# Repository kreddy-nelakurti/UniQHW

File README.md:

# UniQHW

The hardware repository for UQ Phone (UniQ)
The Corresponding software component can be found [https://github.com/Benksur/UniQOS](https://github.com/Benksur/UniQOS)

## About

**Supervised by:** Professor Pauline Pounds  
**Institution:** University of Queensland
<div align="center">

### UQ Phone Team (Year 1 - 2025)

| Name | Role |
|------|------|
| **Ty Behnke** | Firmware Design |
| **James Wood** | Hardware Design |
| **Caiyan Jin** | UI/UX Design |
</div>

Any Questions about the PCB and Schematics please direct them to [james.brian.wood@outlook.com](james.brian.wood@outlook.com)

## Production

The V0.2.0 PCB's must be made with the following specifications from JLCPCB

### Main PCB

This 6-Layer PCB must be made with the following

- Via Covering:	Epoxy Filled & Capped
- Min via hole size/diameter:	0.2mm/(0.3/0.35mm)

The following are also required if meeting the full size specifications of UniQ

- PCB Thickness:	0.8mm

Production versions should also be made with the following (Dependant on desired finish)

- Surface Finish:	ENIG Gold Thickness: 2U"
- PCB Color:	Black
- Silkscreen:	White

### Secondary PCB (Cellular Board)

This 4-Layer PCB must be made with the following

- PCB Thickness:	0.6mm
- Via Covering:	Epoxy Filled & Capped
- Min via hole size/diameter:	0.2mm/(0.3/0.35mm)
- Specify Stackup:	yes JLC04061H-2116

If Either the thickness or stackup is to change this boards traces should be redesigned for 50Ohm Impedance 

Production versions should also be made with the following (Dependant on desired finish)

- Surface Finish:	ENIG Gold Thickness: 2U"
- PCB Color:	Black
- Silkscreen:	White

## Current Issues And Improvements

The V0.2.0 PCB currently suffers from several issues which should be rectified on later versions:

- Batter Connector Location: move so it can be inserted and removed indpendantly of the secondary PCB
- SD/SIM Socket: Tie 3.3v SD card rail to insertion detection to prevent hot-plugging
- Debug Pads: Consider moving to provide easier access without interferance from screen
- Soft Power: Add soft power switch for more agressive power-off functionality and safer power-downs

The following may also be investigated for benefit 
- Improve Display: Ideally Display utilises a parellel interface, this needs more investigation
- Audio Volume: Current speaker is quiet, this should be investigated further to see if this can be remediated in firmware first
- USB Support: Add USB data connectivity to the device for file transfer or programming, this may resolve debug pad issues
- BT Audio: this poses significant challenges, although may be worth while, investigate further

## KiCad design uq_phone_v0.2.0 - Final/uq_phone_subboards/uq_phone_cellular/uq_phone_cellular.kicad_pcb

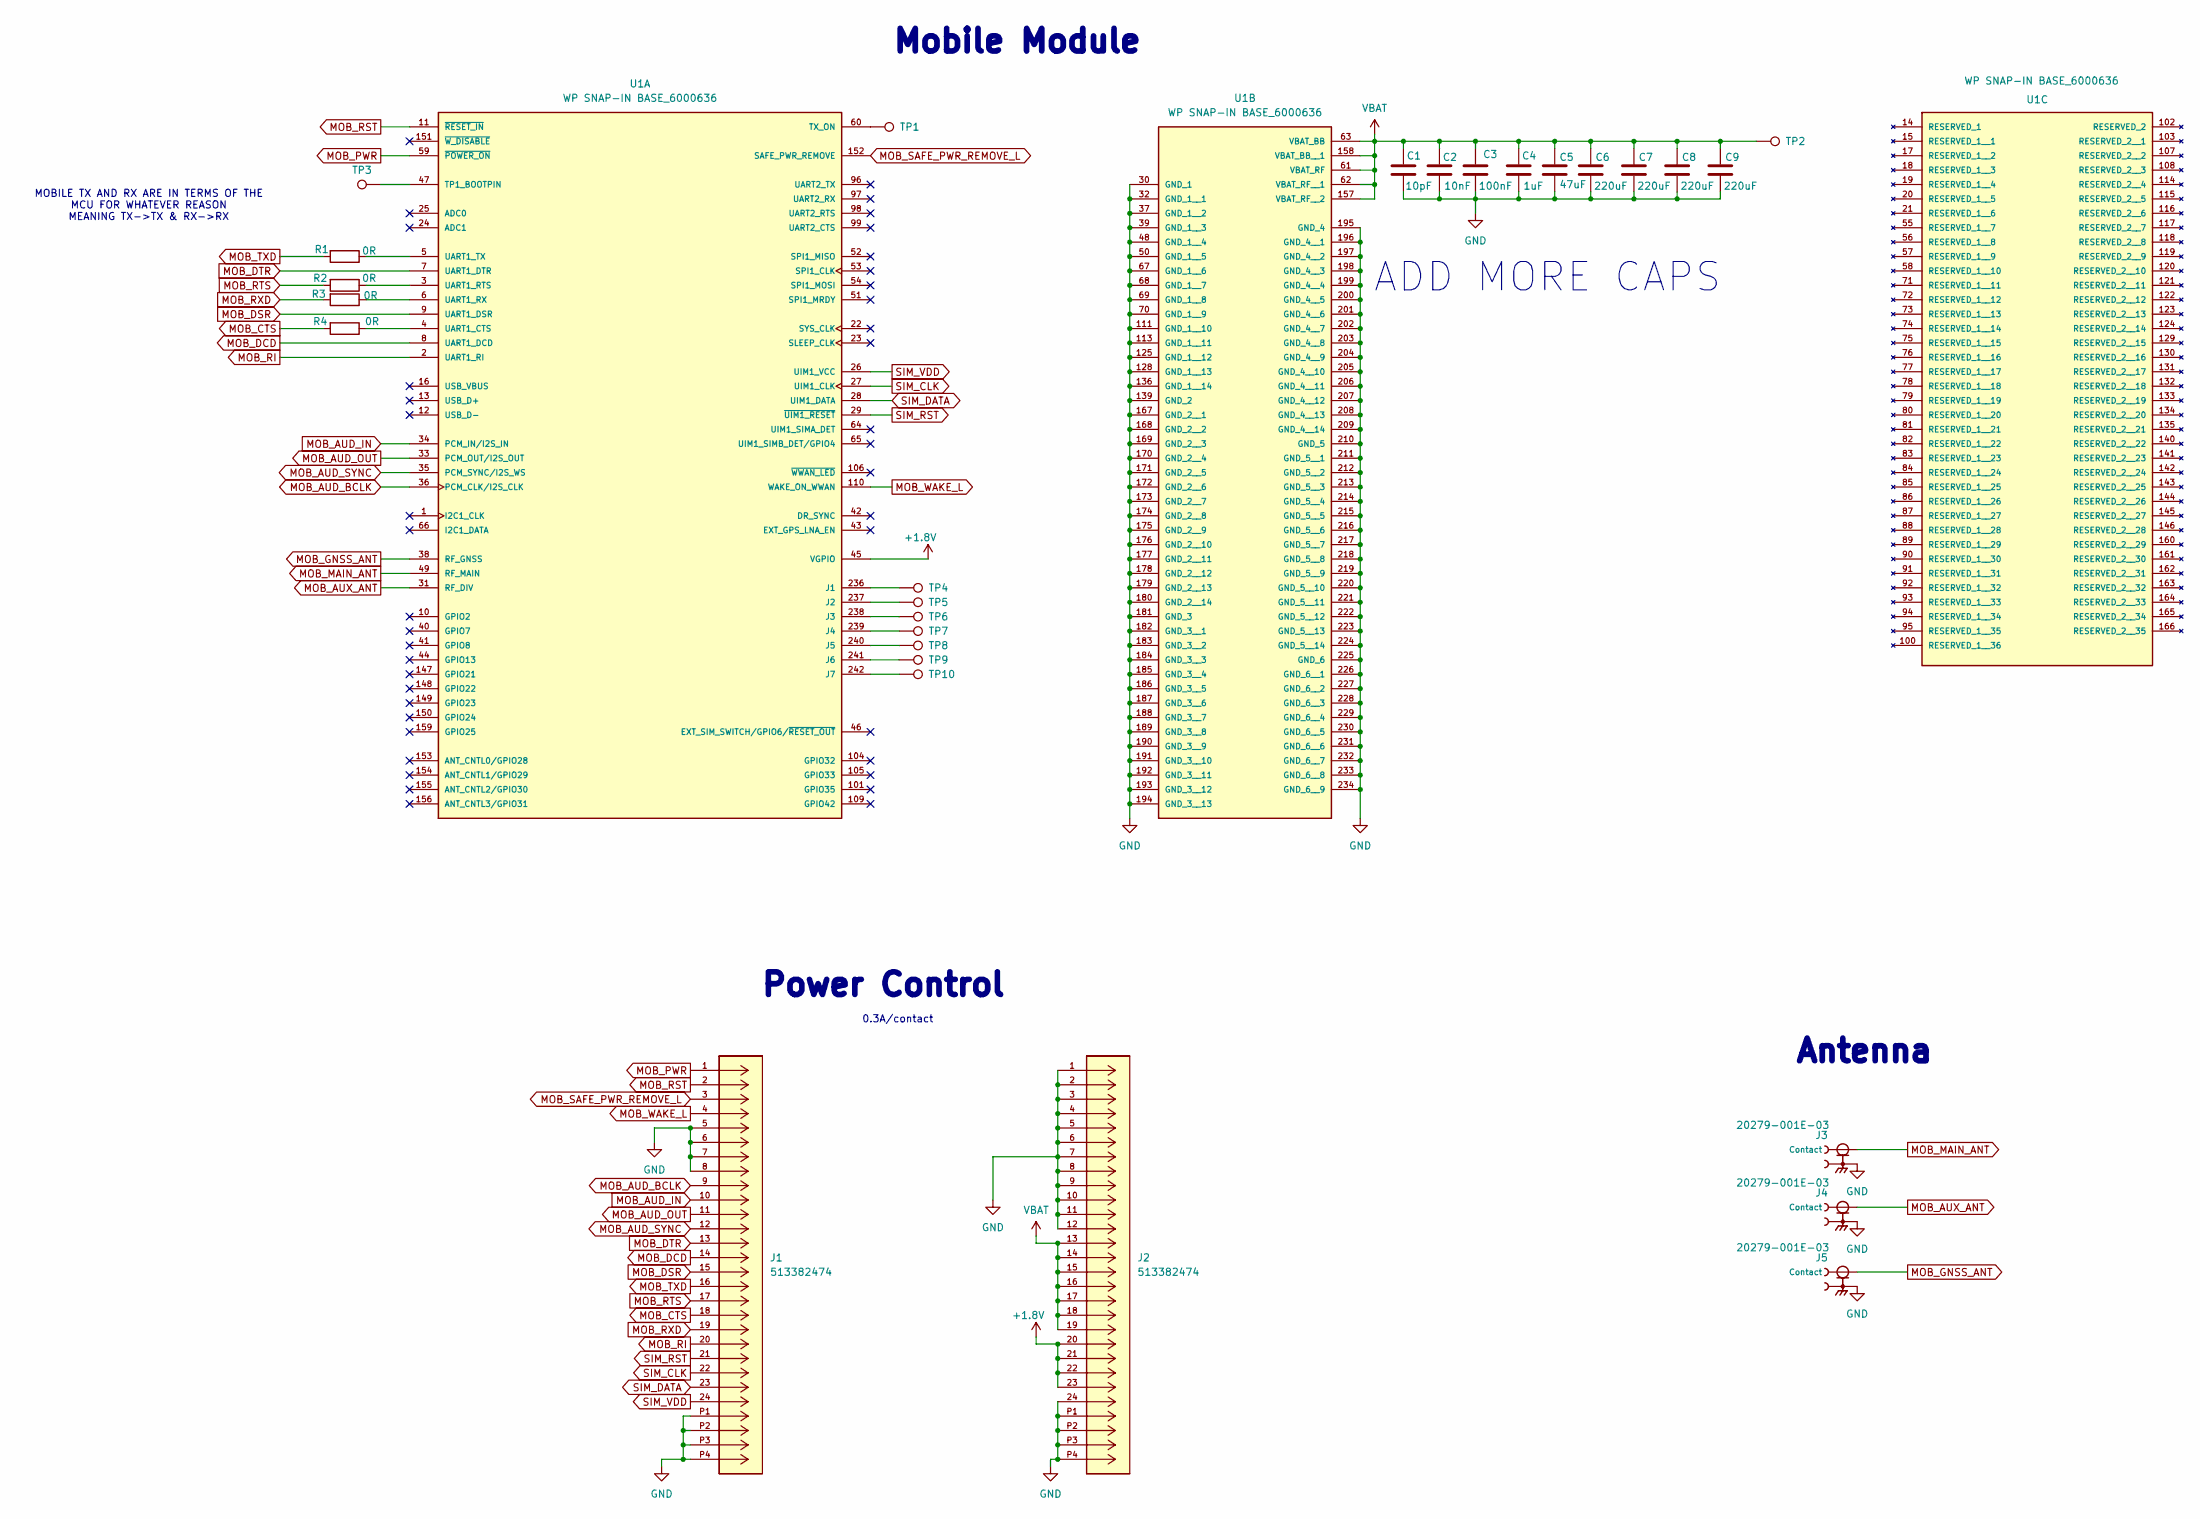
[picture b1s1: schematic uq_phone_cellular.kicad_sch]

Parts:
C1: 10pF; C_0402_1005Metric; LCSC PN C2168222
C2: 10nF; C_0402_1005Metric; LCSC PN C15195
C3: 100nF; C_0201_0603Metric; LCSC PN C160831
C4: 1uF; C_0201_0603Metric; LCSC PN C53067
C5: 47uF; C_0805_2012Metric; LCSC PN C109461
C6, C7, C8, C9: 220uF; C_1206_3216Metric; LCSC PN C412252
J1, J2: 513382474; CON_513382474; MANUFACTURER_PART_NUMBER 513382474; DigiKey_Part_Number WM8960TR-ND
J3, J4, J5: 20279-001E-03; IPEX_20279-001E-03; PARTREV 32; LCSC PN C36499136
R1, R2, R3, R4: 0R; R_0402_1005Metric; LCSC PN C60485
TP1, TP2, TP3, TP4, TP5, TP6, TP7, TP8, TP9, TP10: TestPoint; TestPoint_Pad_D1.5mm
U1: WP SNAP-IN BASE_6000636; XCVR_RC7620_1104625; PARTREV 12

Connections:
+1.8V: J2.20, J2.21, J2.22, J2.23, U1.45 (VGPIO)
GND: C1.2, C2.2, C3.2, C4.2, C5.2, C6.2, C7.2, C8.2, C9.2, J1.5, J1.6, J1.7, J1.8, J1.P1, J1.P2, J1.P3, J1.P4, J2.1, J2.2, J2.3, J2.4, J2.5, J2.6, J2.7, J2.8, J2.9, J2.10, J2.11, J2.12, J2.24, J2.P1, J2.P2, J2.P3, J2.P4, J3.2, J4.2, J5.2, U1.30 (GND_1), U1.32 (GND_1__1), U1.37 (GND_1__2), U1.39 (GND_1__3), U1.48 (GND_1__4), U1.50 (GND_1__5), U1.67 (GND_1__6), U1.68 (GND_1__7), U1.69 (GND_1__8), U1.70 (GND_1__9), U1.111 (GND_1__10), U1.113 (GND_1__11), U1.125 (GND_1__12), U1.128 (GND_1__13), U1.136 (GND_1__14), U1.139 (GND_2), U1.167 (GND_2__1), U1.168 (GND_2__2), U1.169 (GND_2__3), U1.170 (GND_2__4), U1.171 (GND_2__5), U1.172 (GND_2__6), U1.173 (GND_2__7), U1.174 (GND_2__8), U1.175 (GND_2__9), U1.176 (GND_2__10), U1.177 (GND_2__11), U1.178 (GND_2__12), U1.179 (GND_2__13), U1.180 (GND_2__14), U1.181 (GND_3), U1.182 (GND_3__1), U1.183 (GND_3__2), U1.184 (GND_3__3), U1.185 (GND_3__4), U1.186 (GND_3__5), U1.187 (GND_3__6), U1.188 (GND_3__7), U1.189 (GND_3__8), U1.190 (GND_3__9), U1.191 (GND_3__10), U1.192 (GND_3__11), U1.193 (GND_3__12), U1.194 (GND_3__13), U1.195 (GND_4), U1.196 (GND_4__1), U1.197 (GND_4__2), U1.198 (GND_4__3), U1.199 (GND_4__4), U1.200 (GND_4__5), U1.201 (GND_4__6), U1.202 (GND_4__7), U1.203 (GND_4__8), U1.204 (GND_4__9), U1.205 (GND_4__10), U1.206 (GND_4__11), U1.207 (GND_4__12), U1.208 (GND_4__13), U1.209 (GND_4__14), U1.210 (GND_5), U1.211 (GND_5__1), U1.212 (GND_5__2), U1.213 (GND_5__3), U1.214 (GND_5__4), U1.215 (GND_5__5), U1.216 (GND_5__6), U1.217 (GND_5__7), U1.218 (GND_5__8), U1.219 (GND_5__9), U1.220 (GND_5__10), U1.221 (GND_5__11), U1.222 (GND_5__12), U1.223 (GND_5__13), U1.224 (GND_5__14), U1.225 (GND_6), U1.226 (GND_6__1), U1.227 (GND_6__2), U1.228 (GND_6__3), U1.229 (GND_6__4), U1.230 (GND_6__5), U1.231 (GND_6__6), U1.232 (GND_6__7), U1.233 (GND_6__8), U1.234 (GND_6__9)
MOB_AUD_BCLK: J1.9, U1.36 (PCM_CLK/I2S_CLK)
MOB_AUD_IN: J1.10, U1.34 (PCM_IN/I2S_IN)
MOB_AUD_OUT: J1.11, U1.33 (PCM_OUT/I2S_OUT)
MOB_AUD_SYNC: J1.12, U1.35 (PCM_SYNC/I2S_WS)
MOB_AUX_ANT: J4.1 (Contact), U1.31 (RF_DIV)
MOB_CTS: J1.18, R4.2
MOB_DCD: J1.14, U1.8 (UART1_DCD)
MOB_DSR: J1.15, U1.9 (UART1_DSR)
MOB_DTR: J1.13, U1.7 (UART1_DTR)
MOB_GNSS_ANT: J5.1 (Contact), U1.38 (RF_GNSS)
MOB_MAIN_ANT: J3.1 (Contact), U1.49 (RF_MAIN)
MOB_PWR: J1.1, U1.59 (~POWER_ON)
MOB_RI: J1.20, U1.2 (UART1_RI)
MOB_RST: J1.2, U1.11 (~RESET_IN)
MOB_RTS: J1.17, R2.2
MOB_RXD: J1.19, R3.2
MOB_SAFE_PWR_REMOVE_L: J1.3, U1.152 (SAFE_PWR_REMOVE)
MOB_TXD: J1.16, R1.2
MOB_WAKE_L: J1.4, U1.110 (WAKE_ON_WWAN)
unnamed: TP4.1, U1.236 (J1)
unnamed: TP5.1, U1.237 (J2)
unnamed: TP6.1, U1.238 (J3)
unnamed: TP7.1, U1.239 (J4)
unnamed: TP8.1, U1.240 (J5)
unnamed: TP9.1, U1.241 (J6)
unnamed: TP10.1, U1.242 (J7)
unnamed: TP3.1, U1.47 (TP1_BOOTPIN)
unnamed: TP1.1, U1.60 (TX_ON)
unnamed: R4.1, U1.4 (UART1_CTS)
unnamed: R2.1, U1.3 (UART1_RTS)
unnamed: R3.1, U1.6 (UART1_RX)
unnamed: R1.1, U1.5 (UART1_TX)
SIM_CLK: J1.22, U1.27 (UIM1_CLK)
SIM_DATA: J1.23, U1.28 (UIM1_DATA)
SIM_RST: J1.21, U1.29 (~UIM1_RESET)
SIM_VDD: J1.24, U1.26 (UIM1_VCC)
VBAT: C1.1, C2.1, C3.1, C4.1, C5.1, C6.1, C7.1, C8.1, C9.1, J2.13, J2.14, J2.15, J2.16, J2.17, J2.18, J2.19, TP2.1, U1.61 (VBAT_RF), U1.62 (VBAT_RF__1), U1.63 (VBAT_BB), U1.157 (VBAT_RF__2), U1.158 (VBAT_BB__1)

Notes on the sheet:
ADD MORE CAPS
Antenna
Power Control
MOBILE TX AND RX ARE IN TERMS OF THE MCU FOR WHATEVER REASON MEANING TX->TX & RX->RX
0.3A/contact
Mobile Module

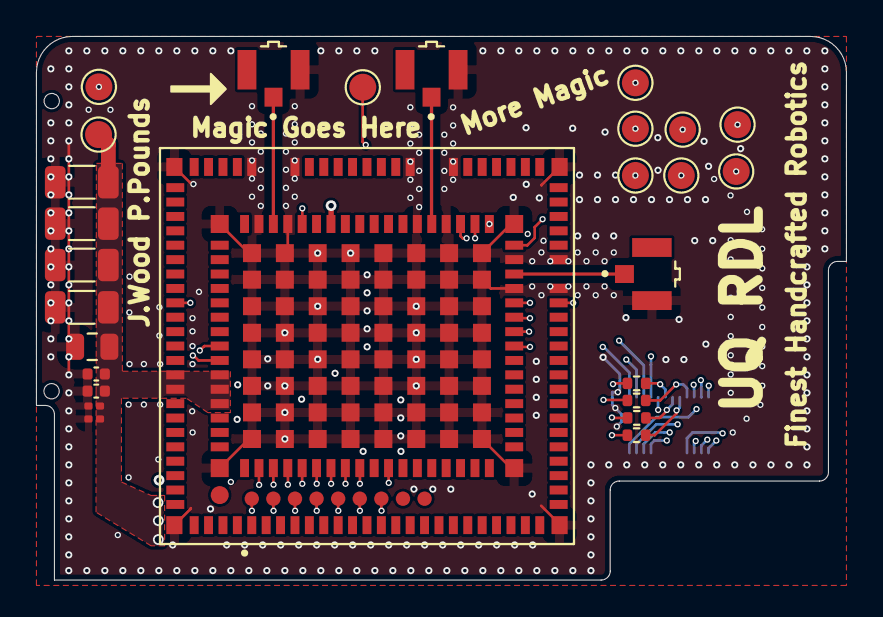
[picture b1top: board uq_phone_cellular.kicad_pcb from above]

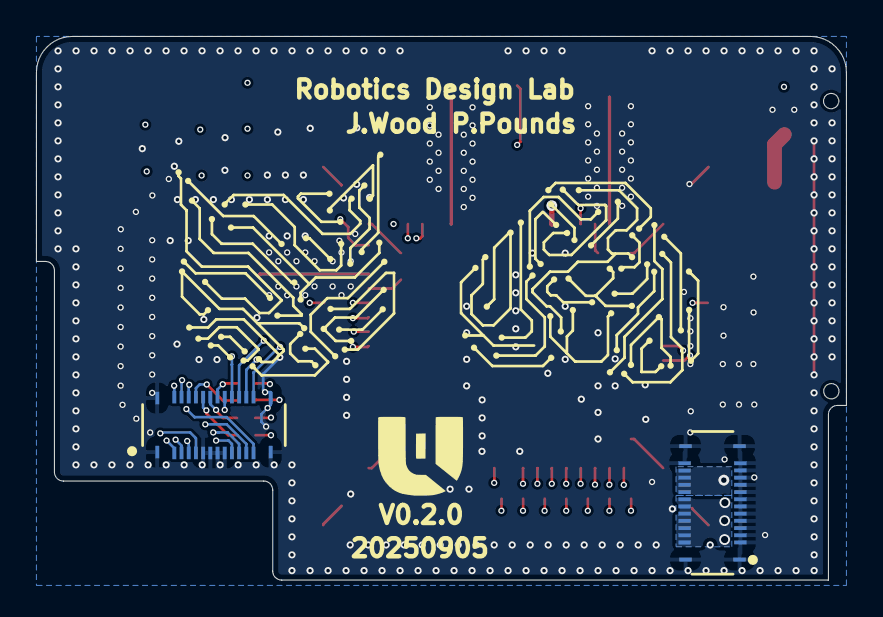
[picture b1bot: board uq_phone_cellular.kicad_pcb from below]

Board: 4 copper layers, 45.0 x 30.2 mm, 29 parts (2 on the bottom side), 39 nets.

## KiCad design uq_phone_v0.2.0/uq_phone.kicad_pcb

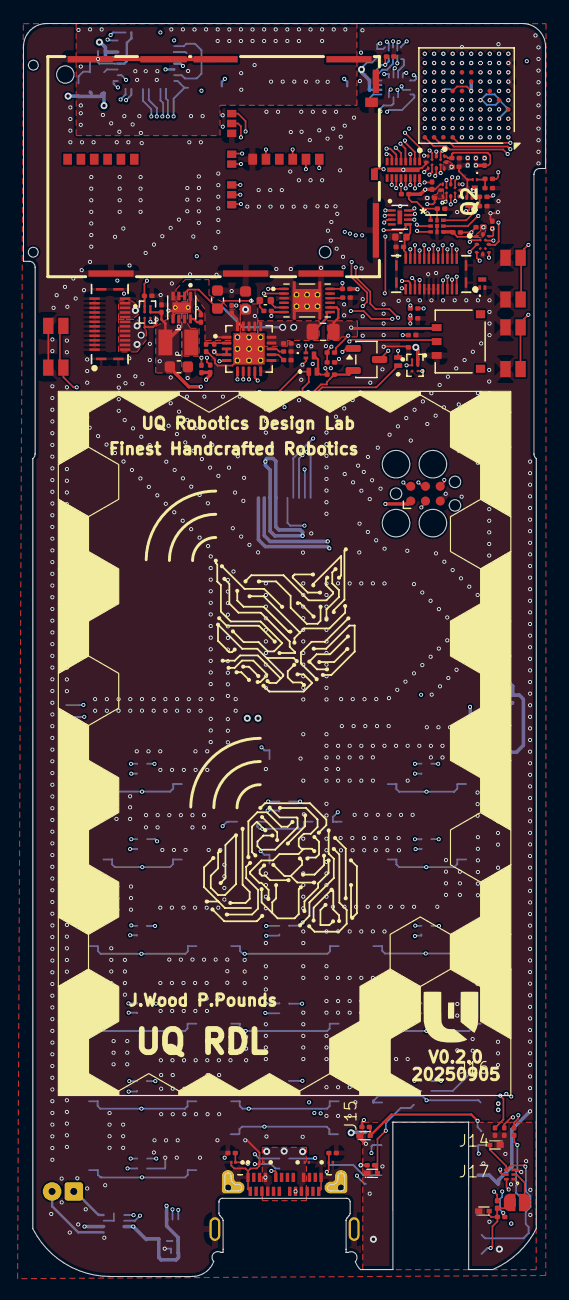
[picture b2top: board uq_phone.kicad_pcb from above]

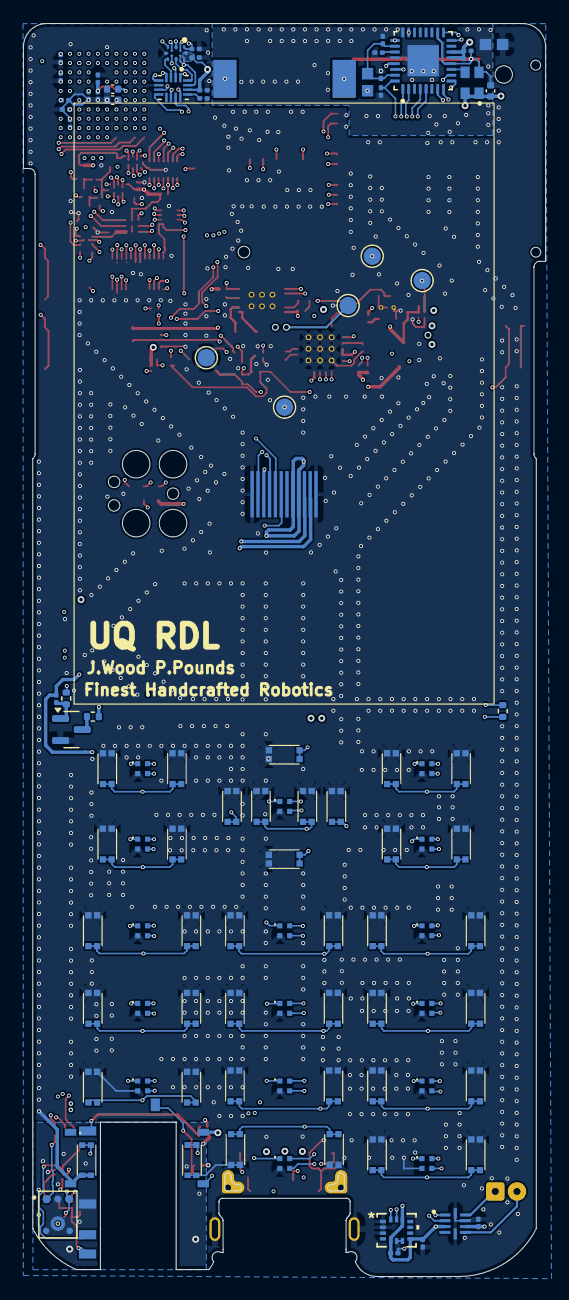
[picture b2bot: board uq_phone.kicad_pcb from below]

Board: 6 copper layers, 45.0 x 108.0 mm, 200 parts (100 on the bottom side), 182 nets.

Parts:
ART: Art_large
C1, C3: 10uF; C_0603_1608Metric
C2: 22uF; C_0603_1608Metric
C4, C7, C14, C36, C39, C40, C41, C42, C43, C44: 4.7uF; C_0201_0603Metric
C5: 470pF; C_0402_1005Metric
C6, C22, C23, C30, C37, C45, C47, C48, C49: 1uF; C_0201_0603Metric
C15, C16, C17, C18, C19, C20, C21, C28, C29, C31, C32, C34, C35, C38, C50, C51, C54, C55, C56, C57, C58, C59, C60: 100nF; C_0201_0603Metric
C25, C26: 2.2uF; C_0402_1005Metric
C33: 33pF; C_0402_1005Metric
C46: 10nF; C_0402_1005Metric
D2, D12: BAT54LP-7; DESD3V3S1BL7B
D4, D5, D6, D7: ESD441DPLR; DIODFN60X30X32-2N
D8, D9, D10, D11: ESD5451X; WBFBP-02C_L1.0-W0.6-BI
DISP1: HS20HS072RX; Display
FB1, FB2: BLM18SG221TN1D; BEADC1608X65N
J2: 124018312112A; AMPHENOL_124018312112A
J3: BM03B-ACHSS-GAN-TF_LF__SN_; JST_BM03B-ACHSS-GAN-TF_LF__SN_
J6: Conn_ARM_SWD_TagConnect_TC2030; Tag-Connect_TC2030-IDC-FP_2x03_P1.27mm_Vertical
J7, J9: 559092474; CON_559092474
J8: MCS-302S-C1; SIM-SMD_MCS-302S-C1
J13, J14, J15, J16, J17: Conn_01x01; Breakout_Mating_Pad
JP1: SolderJumper; SolderJumper-2_P1.3mm_Open_RoundedPad1.0x1.5mm
L1: 3.3uH; INDC2520X120N
LED1, LED3, LED4, LED5, LED6, LED7, LED8, LED9, LED10, LED11, LED12, LED13, LED14, LED15, LED16, LED17: XL-1010RGBC; XL-1010RGBC-WS2812B
LED2: XL-1010RGBC; XL-1010RGBC-Alt
M1: C08-00A; Motor_8mm
MK1: AMM-3738-B-R; MIC_AMM-3738-B-R
OSC1: OT7EL89CJI-111YLC-19.2M; OSC-SMD_4P-L2.0-W1.6-BL
Q1: MMBT3904LP-7; DFN101X61X53-3N
Q2, Q5, Q6: MMBT3904LP-7; MMBT3904LP7
Q3: S8050; SOT-23
Q4: DMP2035U-7; SOT-23-3
R1, R7, R11, R28, R29, R30: 100k; R_0201_0603Metric
R2, R3, R6: 5.1k; R_0201_0603Metric
R4, R16, R17, R22, R31: 4.7k; R_0201_0603Metric
R5: 270k; R_0201_0603Metric
R8, R20, R21, R23, R24, R25, R33, R37: 10k; R_0201_0603Metric
R9: 10m; R_0805_2012Metric
R10, R36: 2.2k; R_0201_0603Metric
R18, R19, R34: 47k; R_0201_0603Metric
R26: 1k; R_0402_1005Metric
R27: 5R; R_0402_1005Metric
R42: 330R; R_0402_1005Metric
SP1: MCABS-258-RC
SW1, SW2, SW3, SW4, SW5, SW7, SW8, SW9, SW10, SW11, SW12, SW13, SW14, SW15, SW17, SW18, SW19, SW20, SW21, SW23, SW24, SW25, SW26, SW27, SW28, SW29, SW30, SW31, SW32, SW33, SW34, SW35, SW36, SW37, SW38, SW39, SW40, SW41: SKTAAAE010
SW6, SW16, SW22: SKSCLCE010
TP1, TP2, TP3, TP5, TP6: TestPoint; TestPoint_Pad_D1.5mm
U1: TPS62162DSGR; SON50P200X200X80-9N
U2: MCP73871-2CCI_ML; QFN50P400X400X100-21N
U3: BQ27441DRZR-G1A; IC_BQ27441DRZR-G1A
U5: TCA9509MRVHR; RVH8_0P4X0P4
U6: STM32H723VGHx; TFBGA-100_8x8mm_Layout10x10_P0.8mm
U7, U15: TPS22964CYZPR; IC_SN74LVC2G34YZPR
U8: TPD3F303DQDR; SON40P170X135X80-9N
U9: AZV5001RA4-7; DFN1210P6X_L1.2-W1.0-P0.40-BL
U10: TPD8F003DQDR; SON40P135X330X80-17N
U11: LSM6DSVTR; LGA14-L_2P59X3P1X0P5_STM
U12: DRV2603RUNR; QFN50P200X200X80-10N
U13: TS3A5018RSVR; QFN40P260X180X55-16N
U14: NAU88C22YG; QFN50P500X500X80-33N
U17: TXU0204DTRR; DTR0012A-MFG
U18: TXU0304DTRR; DTR0012A-MFG
U19, U20: TXU0104DTRR; DTR0012A-MFG

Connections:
+1.8V: C28.1, C38.1, C41.1, C42.1, C46.1, C50.1, C55.1, C57.1, C59.1, J7.20, J7.21, J7.22, J7.23, OSC1.1 (Tri-state), OSC1.4 (VDD), U5.1 (VCCA), U5.5 (EN), U9.5 (Vcc), U13.14 (V+), U14.13 (VDDC), U14.14 (VDDB), U17.11 (VCCB), U17.12 (OE), U18.1 (VCCA), U18.12 (OE), U19.11 (VCCB), U19.12 (OE), U20.1 (VCCA), U20.12 (OE)
+3.3V: C2.1, C14.1, C15.2, C16.2, C17.2, C18.2, C19.2, C21.2, C22.1, C29.1, C30.1, C34.1, C35.1, C51.1, C54.1, C56.1, C58.1, C60.1, DISP1.8 (IOVCC), DISP1.9 (VCC), FB2.1, J6.1 (VCC), L1.2, R1.2, R4.2, R6.2, R22.2, R23.2, R24.2, R25.2, TP2.1, U1.6 (VOS), U5.8 (VCCB), U6.B2 (VBAT), U6.D2 (VDD), U6.F4 (VDD), U6.F5 (VDD), U6.F7 (PDR_ON), U6.H1 (VDDA), U6.K1 (VDD), U7.A2 (VIN), U7.B2 (VIN), U11.5 (VDD_IO), U11.8 (VDD), U11.12 (CS), U12.3 (LRA/~ERM), U12.7 (VDD), U15.A2 (VIN), U15.B2 (VIN), U17.1 (VCCA), U18.11 (VCCB), U19.1 (VCCA), U20.11 (VCCB)
+3.3V_SW: C31.1, DISP1.10 (LEDA), LED1.2 (VDD), LED2.2 (VDD), LED3.2 (VDD), LED4.2 (VDD), LED5.2 (VDD), LED6.2 (VDD), LED7.2 (VDD), LED8.2 (VDD), LED9.2 (VDD), LED10.2 (VDD), LED11.2 (VDD), LED12.2 (VDD), LED13.2 (VDD), LED14.2 (VDD), LED15.2 (VDD), LED16.2 (VDD), LED17.2 (VDD), R21.2, TP5.1, U15.A1 (VOUT), U15.B1 (VOUT)
AGND: C37.1, C39.2, C40.2, C43.2, C44.2, C45.2, D8.1, D9.1, D10.1, D11.1, FB1.2, J14.1, MK1.2 (GND), MK1.3 (GND__1), MK1.5 (GND__2), MK1.6_1 (GND__3), MK1.6_2 (GND__4), U9.1 (GND), U9.3 (G_Detect), U14.24 (VSSSPK), U14.28 (VSSA), U14.33 (EXP)
AUD_BCLK: U13.5 (COM2), U14.8 (BCLK)
AUD_IN: U13.7 (COM3), U14.9 (ADCOUT)
AUD_OUT: U13.10 (COM4), U14.10 (DACIN)
AUD_SCL: U5.2 (SCLA), U14.16 (SCLK)
AUD_SDA: U5.3 (SDAA), U14.17 (SDIO)
AUD_SW_H: U6.K10 (PD12), U19.2 (A1)
AUD_SW_L: R28.2, U13.15 (IN), U19.10 (B1Y)
AUD_SYNC: U13.2 (COM1), U14.7 (FS)
BAT_THERM: J3.2, U2.5 (THERM)
DISP_BL: R26.2, U6.J3 (PA6)
DISP_CS: DISP1.2 (CS), U6.J8 (PB13)
DISP_DC: DISP1.3 (RS), U6.H8 (PD14)
DISP_LEDK: DISP1.11 (LEDK), R27.2
DISP_RESET: DISP1.6 (RESET), U6.G8 (PD15)
DISP_SCL: DISP1.4 (SCL), U6.J6 (PE12)
DISP_SDA: DISP1.5 (SDA), U6.G7 (PE14)
FUEL_GPO: R6.1, U3.12 (GPOUT), U6.G9 (PD11)
GND: C1.1, C2.2, C3.2, C4.2, C5.2, C6.2, C7.2, C14.2, C15.1, C16.1, C17.1, C18.1, C19.1, C20.1, C21.1, C22.2, C23.2, C25.2, C26.2, C28.2, C29.2, C30.2, C31.2, C32.2, C33.2, C34.2, C35.2, C38.2, C41.2, C42.2, C46.2, C50.2, C51.2, C54.2, C55.2, C56.2, C57.2, C58.2, C59.2, C60.2, D4.2, D5.2, D6.2, D7.2, DISP1.1 (GND), DISP1.12 (GND), FB1.1, J2.A1 (GND_A), J2.A12 (GND_A__1), J2.B1 (GND_B), J2.B12 (GND_B__1), J2.SH1 (SHIELD), J2.SH2 (SHIELD__1), J2.SH3 (SHIELD__2), J2.SH4 (SHIELD__3), J3.1, J6.5 (GND), J7.1, J7.2, J7.3, J7.4, J7.5, J7.6, J7.7, J7.8, J7.9, J7.10, J7.11, J7.12, J7.24, J7.P1, J7.P2, J7.P3, J7.P4, J8.6 (VSS), J8.12 (SIM_1_GND), J8.22 (S/GND), J8.23 (GND), J9.5, J9.6, J9.7, J9.8, J9.P1, J9.P2, J9.P3, J9.P4, LED1.3 (GND), LED2.3 (GND), LED3.3 (GND), LED4.3 (GND), LED5.3 (GND), LED6.3 (GND), LED7.3 (GND), LED8.3 (GND), LED9.3 (GND), LED10.3 (GND), LED11.3 (GND), LED12.3 (GND), LED13.3 (GND), LED14.3 (GND), LED15.3 (GND), LED16.3 (GND), LED17.3 (GND), OSC1.2 (GND), Q1.2, Q2.2, Q3.2, Q5.2, Q6.2, R2.1, R3.1, R7.1, R8.1, R10.2, R11.1, R18.1, R19.1, R20.1, R28.1, R29.1, R33.1, R34.1, SW1.2, SW1.4, SW2.2, SW2.4, SW3.2, SW3.4, SW4.2, SW4.4, SW5.2, SW5.4, SW6.3, SW6.4, SW7.2, SW7.4, SW8.2, SW8.4, SW9.2, SW9.4, SW10.2, SW10.4, SW11.2, SW11.4, SW12.2, SW12.4, SW13.2, SW13.4, SW14.2, SW14.4, SW15.2, SW15.4, SW16.3, SW16.4, SW17.2, SW17.4, SW18.2, SW18.4, SW19.2, SW19.4, SW20.2, SW20.4, SW21.2, SW21.4, SW22.1, SW22.2, SW23.2, SW23.4, SW24.2, SW24.4, SW25.2, SW25.4, SW26.2, SW26.4, SW27.2, SW27.4, SW28.2, SW28.4, SW29.2, SW29.4, SW30.2, SW30.4, SW31.2, SW31.4, SW32.2, SW32.4, SW33.2, SW33.4, SW34.2, SW34.4, SW35.2, SW35.4, SW36.2, SW36.4, SW37.2, SW37.4, SW38.2, SW38.4, SW39.2, SW39.4, SW40.2, SW40.4, SW41.2, SW41.4, TP6.1, U1.1 (PGND), U1.4 (AGND), U1.5 (FB), U1.9 (EXP), U2.10 (VSS__1), U2.11 (VSS), U2.21 (EP), U3.3 (VSS), U3.13 (EXP), U5.4 (GND), U5.9 (EPAD), U6.C2 (VSS), U6.E4 (VSS), U6.E5 (VSS), U6.E6 (VSS), U6.G1 (VSSA), U6.J1 (VSS), U7.C1 (GND), U8.9 (GND), U10.17 (GND), U11.1 (SDO/SA0), U11.2 (SDX), U11.3 (SCX), U11.6 (GND), U11.7 (GND), U12.5 (GND), U12.8 (GND__1), U12.10 (GND__2), U13.6 (GND), U14.12 (VSSD), U14.18 (MODE), U15.C1 (GND), U17.6 (GND), U18.6 (GND), U19.6 (GND), U20.6 (GND)
HP_DET: U9.6 (OUT), U20.5 (A4)
HP_DET_MCU: U6.J10 (PD13), U20.7 (B4Y)
HP_LEFT: C48.1, U14.30 (LHP)
HP_LEFT_DET: D8.2, J17.1, U9.4 (L_Detect)
HP_MIC: C47.1, U14.4 (RMICP)
HP_MIC_GND: C45.1, U14.5 (RMICN)
HP_RIGHT: C49.1, U14.29 (RHP)
LED_DATA: R42.2, U6.K2 (PA3)
MCP_OUT: C4.1, Q4.2 (S), R30.1, U2.1 (OUT), U2.20 (OUT__1)
MCP_PG: U2.6 (~PG), U6.G10 (PB15)
MCP_STAT1: R24.1, U2.8 (STAT1/*LBO), U6.H10 (PB14)
MCP_STAT2: R23.1, U2.7 (STAT2), U6.H9 (PD10)
MCU_AUD_BCLK_H: U6.H3 (PA5), U19.5 (A4)
MCU_AUD_BCLK_L: U13.3 (NC2), U19.7 (B4Y)
MCU_AUD_OUT_L: U13.12 (NC4), U19.8 (B3Y)
MCU_AUD_OUT_L_H: U6.K3 (PA7), U19.4 (A3)
MCU_AUD_SYNC_H: U6.G3 (PA4), U19.3 (A2)
MCU_AUD_SYNC_L: U13.16 (NC1), U19.9 (B2Y)
MCU_CTS: U6.C10 (PA11), U17.4 (A3Y)
MCU_DCD: U6.C7 (PD3), U18.8 (B3Y)
MCU_DSR: U6.D9 (PA8), U18.9 (B2Y)
MCU_DTR: U6.D8 (PD0), U18.7 (B4)
MCU_PWR_LATCH: R31.2, U6.J4 (PB0)
MCU_RI: U6.F10 (PC6), U18.10 (B1Y)
MCU_RTS: U6.B10 (PA12), U17.3 (A2)
MCU_RXD: U6.D10 (PA10), U17.5 (A4Y)
MCU_TXD: U6.C9 (PA9), U17.2 (A1)
MIC_BIAS: C44.1, MK1.4 (VDD), R36.2, U14.32 (MICBIAS)
MIC_GND: C37.2, U14.2 (LMICN)
MIC_OUT: C36.2, U14.1 (LMICP)
MIC_PIN: C47.2, D11.2, J13.1, JP1.1 (A), R36.1
MOB_AUD_BCLK: J9.9, U13.4 (NO2)
MOB_AUD_IN: J9.10, U13.8 (NO3)
MOB_AUD_OUT: J9.11, U13.11 (NO4)
MOB_AUD_SYNC: J9.12, U13.1 (NO1)
MOB_CTS: J9.18, U17.8 (B3)
MOB_DCD: J9.14, U18.4 (A3)
MOB_DSR: J9.15, U18.3 (A2)
MOB_DTR: J9.13, U18.5 (A4Y)
MOB_PWR: J9.1, Q1.3
MOB_PWR_CTL: R16.2, U6.A2 (PC13)
MOB_RI: J9.20, U18.2 (A1)
MOB_RST: J9.2, Q2.3
MOB_RST_CTL: R17.2, U6.A1 (PC14)
MOB_RTS: J9.17, U17.9 (B2Y)
MOB_RXD: J9.19, U17.7 (B4)
MOB_SAFE_PWR_REMOVE_H: U6.J9 (PD9), U20.9 (B2Y)
MOB_SAFE_PWR_REMOVE_L: J9.3, U20.3 (A2)
MOB_TXD: J9.16, U17.10 (B1Y)
MOB_WAKE_H: U6.K9 (PD8), U20.10 (B1Y)
MOB_WAKE_L: J9.4, U20.2 (A1)
unnamed: C25.1, U6.E7 (VCAP)
unnamed: C26.1, U6.F8 (VCAP)
unnamed: D2.2 (A), Q4.1 (G), Q5.3, R30.2
unnamed: D2.1 (K), D12.1 (K), SW22.3, SW22.4
unnamed: D7.1, J2.A5 (CC1), R2.2
unnamed: D6.1, J2.B5 (CC2), R3.2
unnamed: J8.2 (CD/DAT3), U10.15 (CH2_OUT)
unnamed: J8.5 (CLK), U10.13 (CH4_OUT)
unnamed: J8.3 (CMD), U10.14 (CH3_OUT)
unnamed: J8.7 (DAT0), U10.11 (CH6_OUT)
unnamed: J8.8 (DAT1), U10.10 (CH7_OUT)
unnamed: J8.1 (DAT2), U10.16 (CH1_OUT)
unnamed: J8.11 (SIM_1_CLK), U8.2 (CLK_OUT)
unnamed: J8.14 (SIM_1_DATA), U8.3 (DATA2_OUT)
unnamed: J8.10 (SIM_1_RST), U8.1 (DATA1_OUT)
unnamed: C49.2, D10.2, J15.1
unnamed: C48.2, D9.2, J16.1
unnamed: JP1.2 (B), U9.2 (MIC)
unnamed: LED1.4 (DI), LED5.1 (DO)
unnamed: LED1.1 (DO), LED2.4 (DI)
unnamed: LED3.4 (DI), LED8.1 (DO)
unnamed: LED3.1 (DO), LED4.4 (DI)
unnamed: LED4.1 (DO), LED5.4 (DI)
unnamed: LED6.1 (DO), LED7.4 (DI)
unnamed: LED7.1 (DO), LED8.4 (DI)
unnamed: LED9.1 (DO), LED10.4 (DI)
unnamed: LED10.1 (DO), LED11.4 (DI)
unnamed: LED6.4 (DI), LED11.1 (DO)
unnamed: LED12.4 (DI), LED17.1 (DO)
unnamed: LED12.1 (DO), LED13.4 (DI)
unnamed: LED13.1 (DO), LED14.4 (DI)
unnamed: LED9.4 (DI), LED14.1 (DO)
unnamed: LED15.4 (DI), R42.1
unnamed: LED15.1 (DO), LED16.4 (DI)
unnamed: LED16.1 (DO), LED17.4 (DI)
unnamed: M1.1 (+), U12.9 (OUT_P)
unnamed: M1.2 (-), U12.6 (OUT_M)
unnamed: C36.1, MK1.1 (OUTPUT)
unnamed: OSC1.3 (OUT), U14.11 (MCLK)
unnamed: Q1.1, R16.1, R18.2
unnamed: Q2.1, R17.1, R19.2
unnamed: Q3.1, R21.1, R26.1
unnamed: Q3.3, R27.1
unnamed: Q5.1, R31.1, R34.2
unnamed: Q6.1, R37.1
unnamed: R1.1, U1.8 (PG)
unnamed: L1.1, U1.7 (SW)
unnamed: R10.1, U2.13 (PROG1)
unnamed: R11.2, U2.12 (PROG3)
unnamed: R5.1, R7.2, U2.2 (VPCC)
unnamed: C6.1, J3.3, R9.1, U3.6 (BAT), U3.8 (SRP)
unnamed: R8.2, U3.10 (BIN)
unnamed: C5.1, U3.5 (VDD)
unnamed: R20.2, U6.D5 (BOOT0)
unnamed: R33.2, U13.13 (~EN)
unnamed: C39.1, C40.1, FB2.2, U14.26 (VDDSPK), U14.31 (VDDA)
unnamed: C43.1, U14.27 (VREF)
PB_0: SW34.1, SW34.3, SW39.1, SW39.3, U6.A3 (PE2)
PB_1: SW24.1, SW24.3, SW28.1, SW28.3, U6.C3 (PE4)
PB_2: SW25.1, SW25.3, SW29.1, SW29.3, U6.A5 (PB7)
PB_3: SW26.1, SW26.3, SW30.1, SW30.3, U6.A6 (PB4(NJTRST))
PB_4: SW12.1, SW12.3, SW18.1, SW18.3, U6.C1 (PH0)
PB_5: SW13.1, SW13.3, SW19.1, SW19.3, U6.C5 (PB5)
PB_6: SW14.1, SW14.3, SW20.1, SW20.3, U6.B6 (PD5)
PB_7: SW1.1, SW1.3, SW7.1, SW7.3, U6.D3 (PE5)
PB_8: SW2.1, SW2.3, SW8.1, SW8.3, U6.C4 (PE1)
PB_9: SW3.1, SW3.3, SW9.1, SW9.3, U6.B5 (PB6)
PB_CALL: SW36.1, SW36.3, SW41.1, SW41.3, U6.B1 (PC15)
PB_DPAD_DOWN: SW17.1, SW17.3, U6.B3 (PE3)
PB_DPAD_LEFT: SW37.1, SW37.3, U6.G4 (PC4)
PB_DPAD_RIGHT: SW32.1, SW32.3, U6.C6 (PD6)
PB_DPAD_SELECT: SW5.1, SW5.3, SW11.1, SW11.3, U6.F1 (PC0)
PB_DPAD_UP: SW23.1, SW23.3, U6.F2 (PC1)
PB_END_CALL: SW15.1, SW15.3, SW21.1, SW21.3, U6.D6 (PD7)
PB_HASH: SW35.1, SW35.3, SW40.1, SW40.3, U6.D4 (PE0)
PB_MENU_L: SW27.1, SW27.3, SW31.1, SW31.3, U6.G2 (PA0)
PB_MENU_R: SW4.1, SW4.3, SW10.1, SW10.3, U6.D7 (PD4)
PB_STAR: SW33.1, SW33.3, SW38.1, SW38.3, U6.E3 (PE6)
PB_VOL_DOWN: SW16.1, SW16.2, U6.H2 (PA1)
PB_VOL_UP: SW6.1, SW6.2, U6.J2 (PA2)
POWER_SW: U6.E8 (PD1), U15.C2 (ON)
PWR_BUTTON_SENSE: D12.2 (A), U6.K8 (PB12)
REG_VIN_SW: C1.2, Q4.3 (D), U1.2 (VIN), U1.3 (EN)
RST: C20.2, J6.3 (~RESET), U6.E1 (NRST)
SCL: R22.1, U3.2 (SCL), U5.7 (SCLB), U6.B4 (PB8), U11.13 (SCL)
SDA: R4.1, U3.1 (SDA), U5.6 (SDAB), U6.A4 (PB9), U11.14 (SDA)
SD_PWR_EN: R29.2, U6.J7 (PB10), U7.C2 (ON)
SD_VDD_SW: C23.1, J8.4 (VDD), U7.A1 (VOUT), U7.B1 (VOUT)
SIM_CLK: J9.22, U8.7 (CLK_IN)
SIM_DATA: J9.23, U8.6 (DATA2_IN)
SIM_RST: J9.21, U8.8 (DATA1_IN)
SIM_VDD: C32.1, C33.1, J8.9 (SIM_1_VCC), J9.24, U8.5 (VCC)
SPEAKER_N: SP1.-, U14.25 (LSPKOUT)
SPEAKER_P: SP1.+, U14.23 (RSPKOUT)
SWCLK: J6.4 (SWCLK), U6.A9 (PA14(JTCK)
SWDIO: J6.2 (SWDIO), U6.A10 (PA13(JTMS)
SWO: J6.6 (SWO), U6.A7 (PB3(JTDO)
VBAT: C7.1, J7.13, J7.14, J7.15, J7.16, J7.17, J7.18, J7.19, R9.2, TP3.1, U2.14 (VBAT__1), U2.15 (VBAT), U2.16 (VBAT_SENSE), U3.7 (SRN)
VIB_EN: U6.K5 (PE9), U12.1 (EN)
VIB_PWM: U6.K4 (PB1), U12.2 (PWM)
VUSB: C3.1, D4.1, D5.1, J2.A4 (VBUS_A), J2.A9 (VBUS_A__1), J2.B4 (VBUS_B), J2.B9 (VBUS_B__1), R5.2, TP1.1, U2.3 (SEL), U2.4 (PROG2), U2.9 (~TE), U2.17 (CE), U2.18 (IN), U2.19 (IN__1)
uSD_CLK: U6.C8 (PC12), U10.4 (CH4_IN)
uSD_CMD: U6.B7 (PD2), U10.3 (CH3_IN)
uSD_DAT0: U6.F9 (PC8), U10.6 (CH6_IN)
uSD_DAT1: U6.E9 (PC9), U10.7 (CH7_IN)
uSD_DAT2: U6.B9 (PC10), U10.1 (CH1_IN)
uSD_DAT3: U6.B8 (PC11), U10.2 (CH2_IN)
uSD_DET: U6.E10 (PC7), U10.5 (CH5_IN)
uSD_TRAY_DET: J8.21 (SW/CD), R25.1, R37.2, U6.K7 (PB11), U10.12 (CH5_OUT)

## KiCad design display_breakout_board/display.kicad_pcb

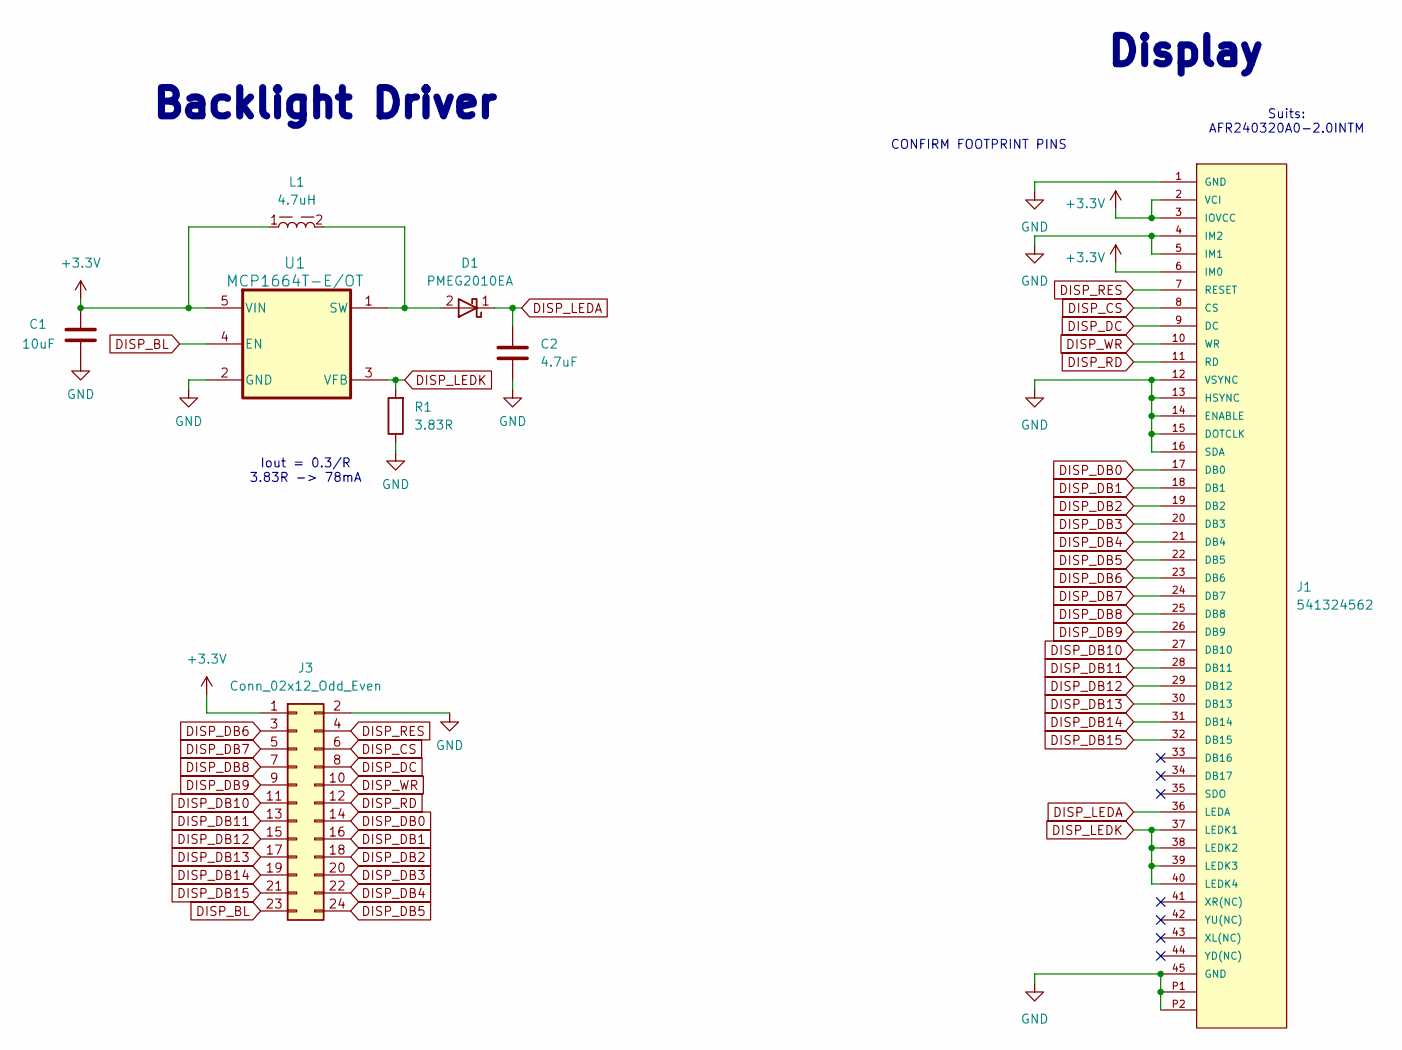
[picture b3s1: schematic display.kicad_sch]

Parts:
C1: 10uF; C_0603_1608Metric
C2: 4.7uF; C_0402_1005Metric
D1: PMEG2010EA; D_SOD-323
J1: 541324562; CON_541324562_MOL; MANUFACTURER_PART_NUMBER 541324562; DigiKey_Part_Number WM8850TR-ND
J3: Conn_02x12_Odd_Even; PinSocket_2x12_P2.54mm_Vertical
L1: 4.7uH; WE-MAPI_3015; DigiKey_Part_Number 732-4866-2-ND
R1: 3.83R; R_0603_1608Metric
U1: MCP1664T-E/OT; SOT-23-5_OT_MCH

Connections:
+3.3V: C1.1, J1.2 (VCI), J1.3 (IOVCC), J1.6 (IM0), J3.1, L1.1, U1.5 (VIN); also elsewhere on the board
DISP_BL: J3.23, U1.4 (EN)
DISP_CS: J1.8 (CS), J3.6; also elsewhere on the board
DISP_DB0: J1.17 (DB0), J3.14; also elsewhere on the board
DISP_DB1: J1.18 (DB1), J3.16; also elsewhere on the board
DISP_DB2: J1.19 (DB2), J3.18; also elsewhere on the board
DISP_DB3: J1.20 (DB3), J3.20; also elsewhere on the board
DISP_DB4: J1.21 (DB4), J3.22; also elsewhere on the board
DISP_DB5: J1.22 (DB5), J3.24; also elsewhere on the board
DISP_DB6: J1.23 (DB6), J3.3; also elsewhere on the board
DISP_DB7: J1.24 (DB7), J3.5; also elsewhere on the board
DISP_DB8: J1.25 (DB8), J3.7; also elsewhere on the board
DISP_DB9: J1.26 (DB9), J3.9; also elsewhere on the board
DISP_DB10: J1.27 (DB10), J3.11; also elsewhere on the board
DISP_DB11: J1.28 (DB11), J3.13; also elsewhere on the board
DISP_DB12: J1.29 (DB12), J3.15; also elsewhere on the board
DISP_DB13: J1.30 (DB13), J3.17; also elsewhere on the board
DISP_DB14: J1.31 (DB14), J3.19; also elsewhere on the board
DISP_DB15: J1.32 (DB15), J3.21; also elsewhere on the board
DISP_DC: J1.9 (DC), J3.8; also elsewhere on the board
DISP_LEDA: C2.1, D1.1 (K), J1.36 (LEDA); also elsewhere on the board
DISP_LEDK: J1.37 (LEDK1), J1.38 (LEDK2), J1.39 (LEDK3), J1.40 (LEDK4), R1.2, U1.3 (VFB); also elsewhere on the board
DISP_RD: J1.11 (RD), J3.12; also elsewhere on the board
DISP_RES: J1.7 (RESET), J3.4; also elsewhere on the board
DISP_WR: J1.10 (WR), J3.10; also elsewhere on the board
GND: C1.2, C2.2, J1.1 (GND), J1.4 (IM2), J1.5 (IM1), J1.12 (VSYNC), J1.13 (HSYNC), J1.14 (ENABLE), J1.15 (DOTCLK), J1.16 (SDA), J1.45 (GND), J1.P1, J1.P2, J3.2, R1.1, U1.2 (GND); also elsewhere on the board
unnamed: D1.2 (A), L1.2, U1.1 (SW)

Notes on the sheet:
Backlight Driver
CONFIRM FOOTPRINT PINS
Display
Suits: AFR240320A0-2.0INTM
Iout = 0.3/R 3.83R -> 78mA

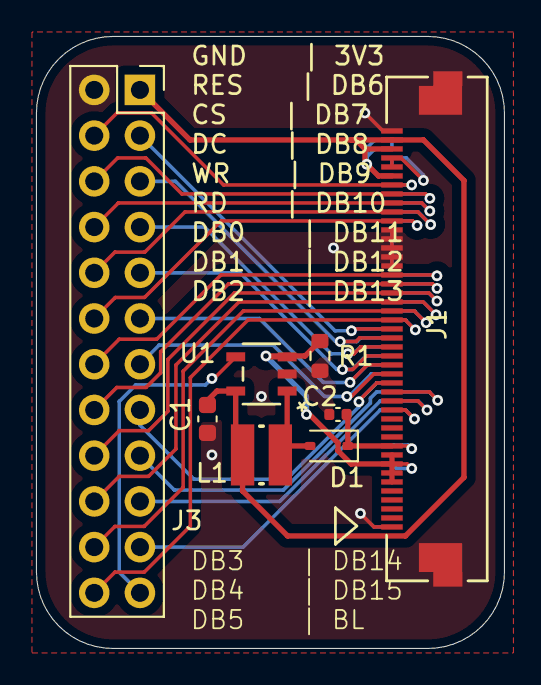
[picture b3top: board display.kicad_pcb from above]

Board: 2 copper layers, 26.0 x 34.0 mm, 9 parts (1 on the bottom side), 27 nets.

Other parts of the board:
J2: 541324562; CON_541324562_MOL

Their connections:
+3.3V: J2.40 (LEDK4), J2.43 (XL(NC)), J2.44 (YD(NC)); also elsewhere on the board
DISP_CS: J2.38 (LEDK2); also elsewhere on the board
DISP_DB0: J2.29 (DB12); also elsewhere on the board
DISP_DB1: J2.28 (DB11); also elsewhere on the board
DISP_DB2: J2.27 (DB10); also elsewhere on the board
DISP_DB3: J2.26 (DB9); also elsewhere on the board
DISP_DB4: J2.25 (DB8); also elsewhere on the board
DISP_DB5: J2.24 (DB7); also elsewhere on the board
DISP_DB6: J2.23 (DB6); also elsewhere on the board
DISP_DB7: J2.22 (DB5); also elsewhere on the board
DISP_DB8: J2.21 (DB4); also elsewhere on the board
DISP_DB9: J2.20 (DB3); also elsewhere on the board
DISP_DB10: J2.19 (DB2); also elsewhere on the board
DISP_DB11: J2.18 (DB1); also elsewhere on the board
DISP_DB12: J2.17 (DB0); also elsewhere on the board
DISP_DB13: J2.16 (SDA); also elsewhere on the board
DISP_DB14: J2.15 (DOTCLK); also elsewhere on the board
DISP_DB15: J2.14 (ENABLE); also elsewhere on the board
DISP_DC: J2.37 (LEDK1); also elsewhere on the board
DISP_LEDA: J2.10 (WR); also elsewhere on the board
DISP_LEDK: J2.6 (IM0), J2.7 (RESET), J2.8 (CS), J2.9 (DC); also elsewhere on the board
DISP_RD: J2.35 (SDO); also elsewhere on the board
DISP_RES: J2.39 (LEDK3); also elsewhere on the board
DISP_WR: J2.36 (LEDA); also elsewhere on the board
GND: J2.1 (GND), J2.30 (DB13), J2.31 (DB14), J2.32 (DB15), J2.33 (DB16), J2.34 (DB17), J2.41 (XR(NC)), J2.42 (YU(NC)), J2.45 (GND), J2.P1, J2.P2; also elsewhere on the board

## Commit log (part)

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2026-02-27 Add libs, mainly SnapEDA
